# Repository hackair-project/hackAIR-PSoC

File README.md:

# hackAIR-PSoC

hackAIR is an open technology platform that you can use to access, collect and improve air quality information in Europe.

This repository contains code and resources for the hackAIR mobile sensor, a Bluetooth-enabled air quality sensor based on PSoC. 

Visit the [repository wiki](http://www.hackair.eu/docs/) for the full documentation, and go to [hackAIR.eu](http://www.hackair.eu/hackair-mobile/) for a more user-friendly tutorial.

hackAIR also has designs for an Arduino or Wemos based hackAIR home air quality sensor, and combines other sources of air quality information for a full map. 

### Licensing

```
hackAIR Arduino Library
Copyright © 2016-2017 hackAir Consortium

This program is free software: you can redistribute it and/or modify
it under the terms of the GNU Lesser General Public License as published
by the Free Software Foundation, either version 3 of the License, or
(at your option) any later version.

This program is distributed in the hope that it will be useful,
but WITHOUT ANY WARRANTY; without even the implied warranty of
MERCHANTABILITY or FITNESS FOR A PARTICULAR PURPOSE.  See the
GNU Lesser General Public License for more details.

You should have received a copy of the GNU Lesser General Public License
along with this program.  If not, see <http://www.gnu.org/licenses/>.
```

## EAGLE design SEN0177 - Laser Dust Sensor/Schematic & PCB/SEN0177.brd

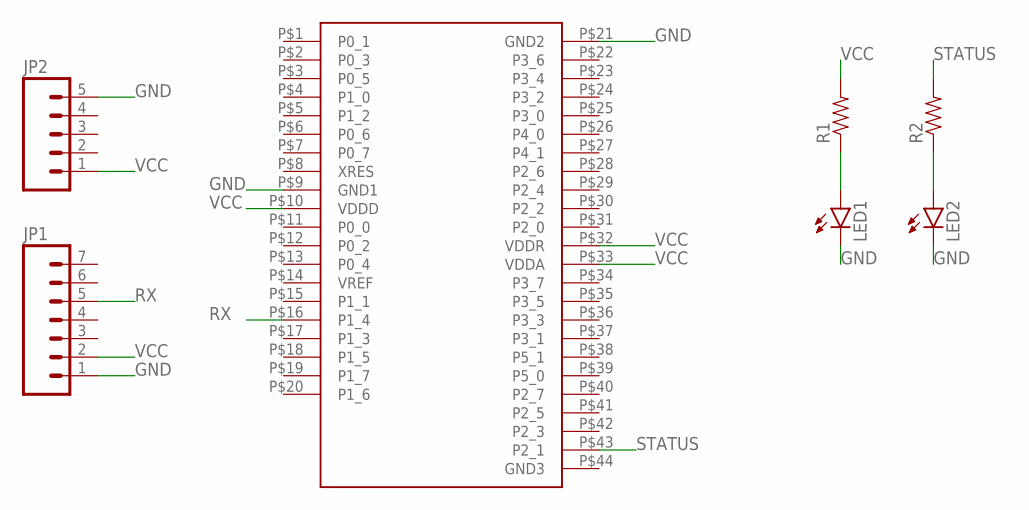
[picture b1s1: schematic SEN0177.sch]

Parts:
JP1: M07LONGPADS; 1X07_LONGPADS
JP2: M05PTH_LONGPADS; 1X05_LONGPADS
LED1, LED2: LED3MM
R1, R2: RESISTORPTH-1/4W; AXIAL-0.4
U$1: CYBLE_MODULE

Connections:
GND: JP1.1, JP2.5, LED1.K (C), LED2.K (C), U$1.P$9 (GND1), U$1.P$21 (GND2)
unnamed: LED1.A, R1.P$1 (1)
unnamed: LED2.A, R2.P$1 (1)
RX: JP1.5, U$1.P$16 (P1_4)
STATUS: R2.P$2 (2), U$1.P$43 (P2_1)
VCC: JP1.2, JP2.1, R1.P$2 (2), U$1.P$10 (VDDD), U$1.P$32 (VDDR), U$1.P$33 (VDDA)

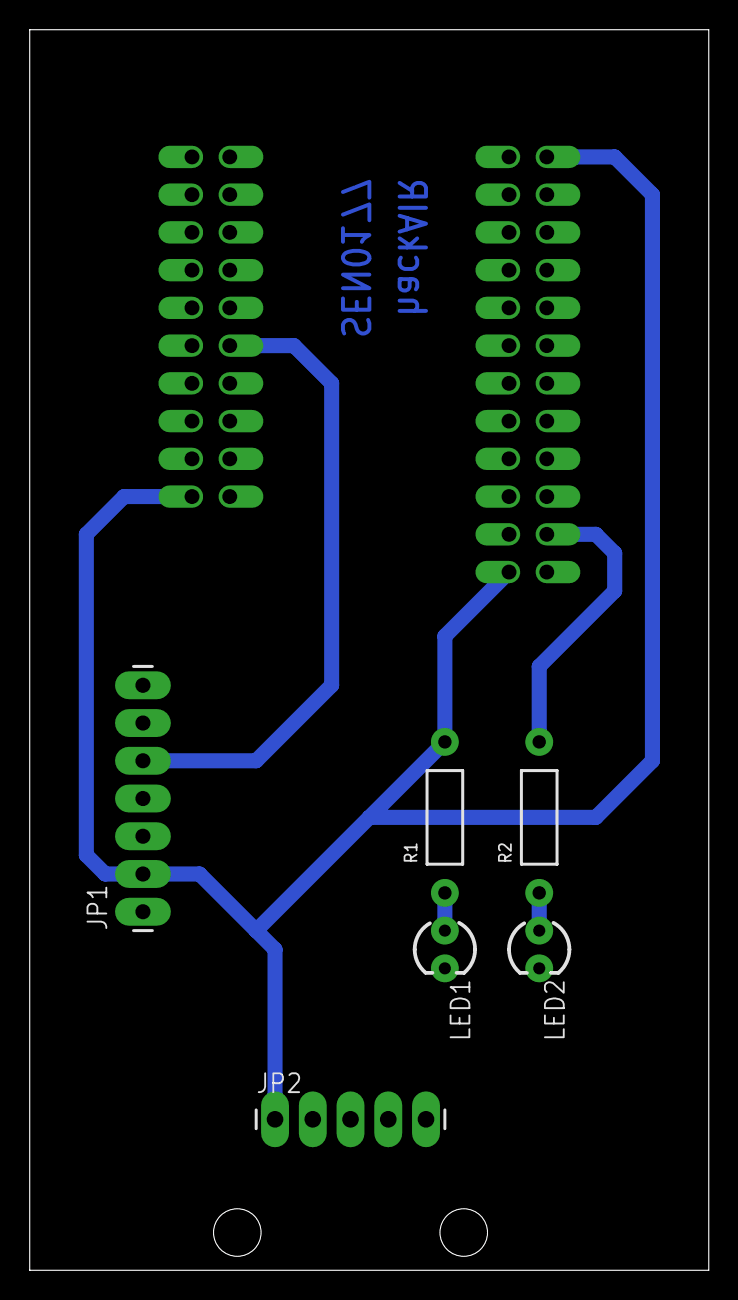
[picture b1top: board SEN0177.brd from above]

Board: 2 copper layers, 45.7 x 83.5 mm, 7 parts (0 on the bottom side), 6 nets.

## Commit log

2017-02-15 [SEN0177] PCB
2017-02-15 [SEN0177] Code
2017-02-21 [SEN0177] Code Update
2017-02-21 [SDS011] Code
2017-02-21 [SDS011] PCB
2017-02-22 [GP2Y1010AU0F] Code
2017-02-22 [GP2Y1010AU0F] PCB
2017-02-22 [DN7C3CA006] PCB
2017-02-22 [DN7C3CA006] Code
2017-02-28 [PPD42] PCB
2017-02-28 [PPD42] Code
2017-03-01 Added PCB Printouts
2017-11-22 Update PSoC Creator Project Version
2017-11-23 Updated cover instructions for the project
2018-05-03 Tiny changes to links + image
2018-05-03 Added LGPL licensing
2018-05-10 Support for CY5676 module
2018-05-13 Mark old versions
2018-10-11 Updated links to documentation

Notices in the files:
parts and their libraries:
SparkFun-Connectors: Licensing: Creative Commons ShareAlike 4.0 International - https://creativecommons.org/licenses/by-sa/4.0
